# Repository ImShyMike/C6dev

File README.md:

# C6dev

A tiny and low power dev board for the ESP32-C6 with 10 GPIO pins, microSD card slot, 64Mbit (8MB) of Quad SPI Flash, USB C 2.0, a step-down converter for efficiency, 2.4 GHz ceramic chip antenna and very cool silkscreen. All pins are labeled with their number, actual GPIO and even other functions.

---

I've been wanting to make a devboard for a while now so i decided to make one with a RISC-V, low power MCU while breaking out a bunch of useful stuff while still keeping an acceptable amount of GPIO.

It was quite a lot harder than I expected with all the datasheet searching and looking up everything to make sure it works but atleast the routing was quite fun.

---

| PCB front | PCB back |
|:---------:|:--------:|
|  |  |

---

## PCB

---

## BOM

| Item | Quantity | Price (USD) |
|:----:|:--------:|:-----------:|
| PCB  |       1  |         $77 |

---

## 3D Model

[STL (renders on GitHub)](PCB/devboard/devboard.stl)

[STEP](PCB/devboard/devboard.stl)

[WRL (best)](PCB/devboard/devboard.wrl)

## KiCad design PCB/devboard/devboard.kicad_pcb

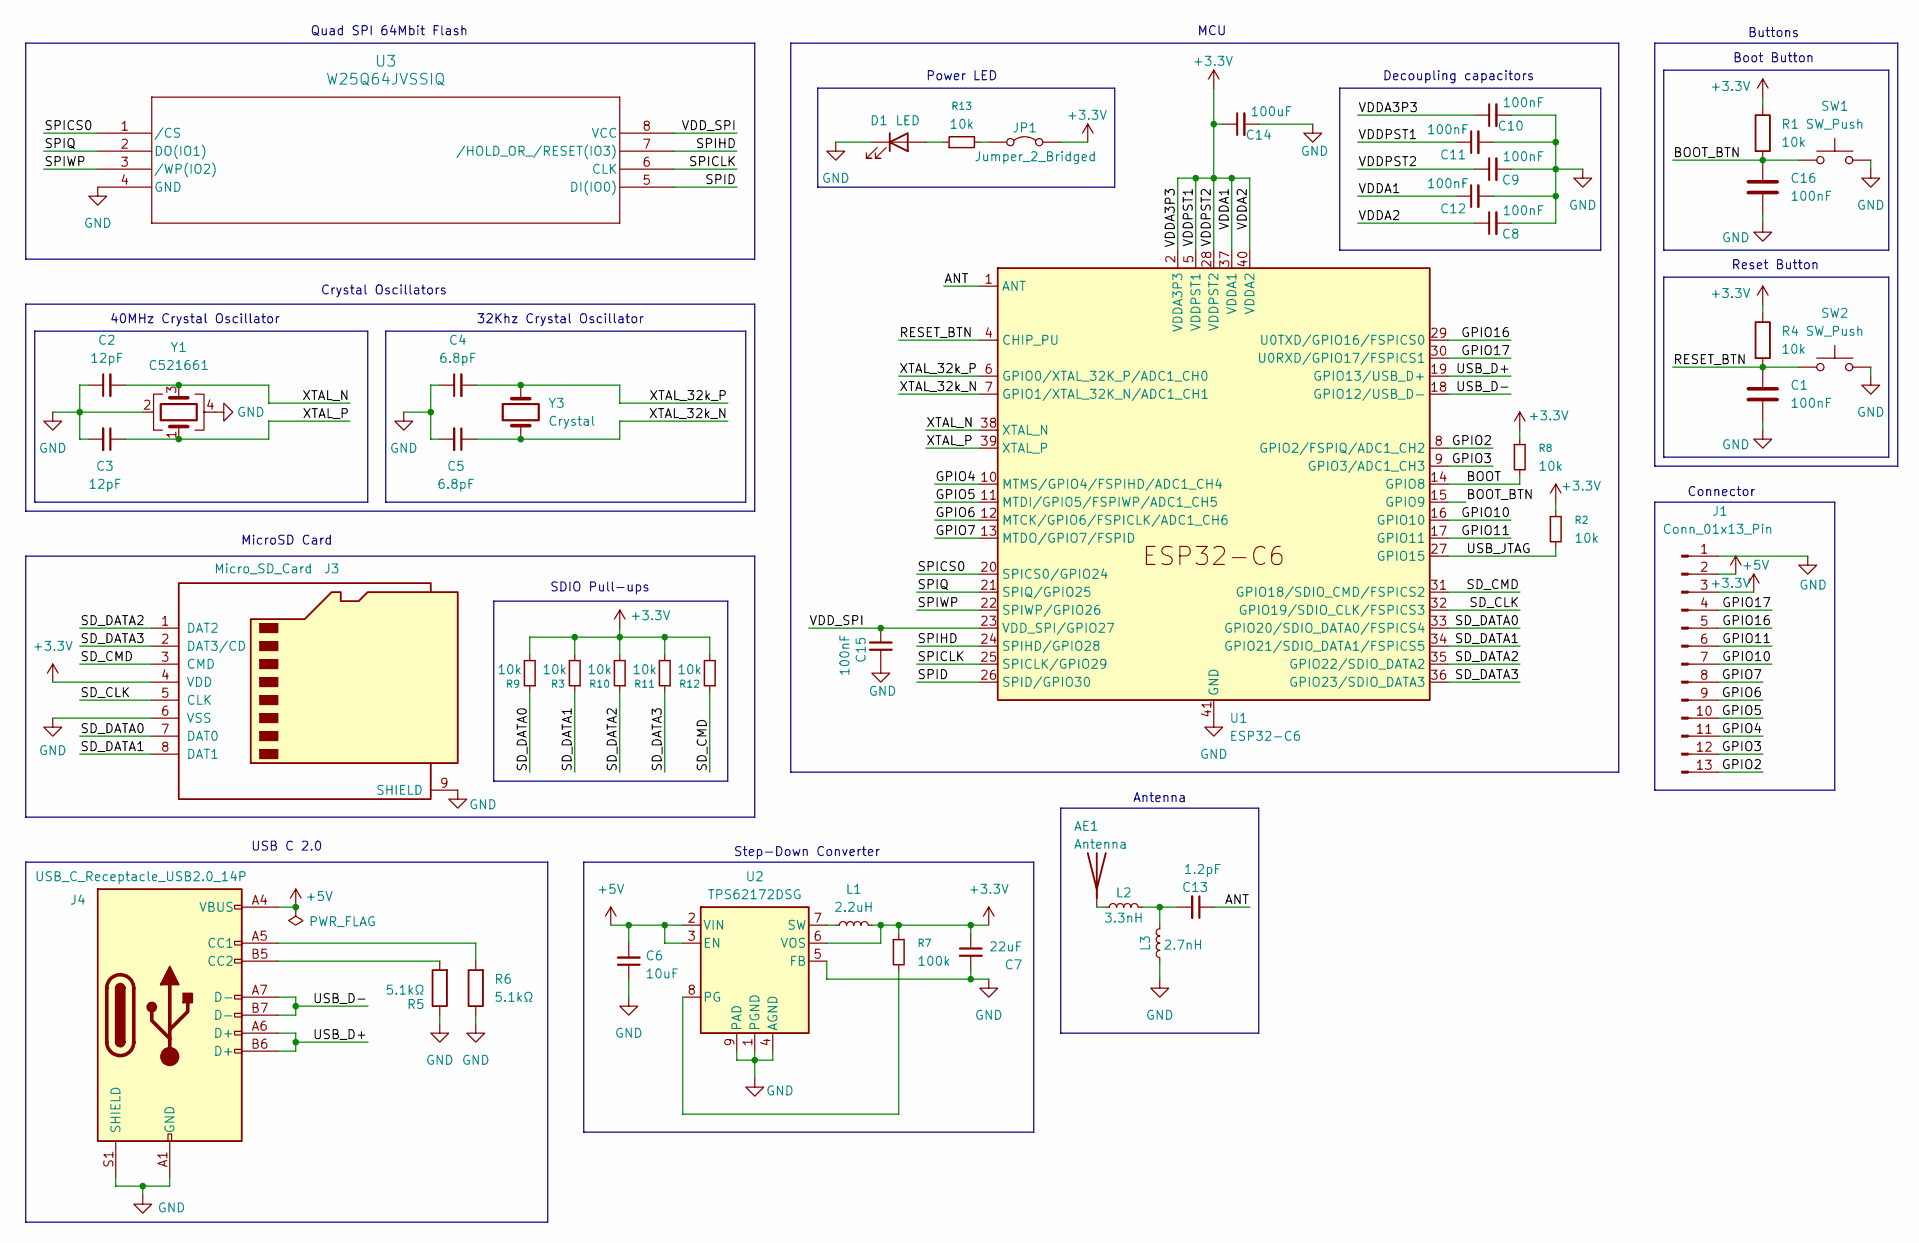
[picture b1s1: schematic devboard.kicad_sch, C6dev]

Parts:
AE1: Antenna; Johanson_2450AT18x100_2400-2500Mhz
C1, C8, C9, C10, C11, C12, C15, C16: 100nF; C_0402_1005Metric
C2, C3: 12pF; C_0402_1005Metric
C4, C5: 6.8pF; C_0402_1005Metric
C6: 10uF; C_0805_2012Metric
C7: 22uF; C_1206_3216Metric
C13: 1.2pF; C_0402_1005Metric
C14: 100uF; CP_EIA-3216-18_Kemet-A
D1: LED; LED_0805_2012Metric
J1: Conn_01x13_Pin; PinHeader_1x13_P2.54mm_Vertical
J3: Micro_SD_Card; microSD_HC_Wuerth_693072010801
J4: USB_C_Receptacle_USB2.0_14P; USB_C_Receptacle_HRO_TYPE-C-31-M-12
JP1: Jumper_2_Bridged; SolderJumper-2_P1.3mm_Open_RoundedPad1.0x1.5mm
L1: 2.2uH; L_0603_1608Metric
L2: 3.3nH; L_0402_1005Metric
L3: 2.7nH; L_0402_1005Metric
R1, R2, R3, R4, R8, R9, R10, R11, R12, R13: 10k; R_0402_1005Metric
R5, R6: 5.1kΩ; R_0402_1005Metric
R7: 100k; R_0402_1005Metric
SW1, SW2: SW_Push; SW_SPST_PTS647_Sx38
U1: ESP32-C6; QFN-40-1EP_5x5mm_P0.4mm_EP3.6x3.6mm
U2: TPS62172DSG; WSON-8-1EP_2x2mm_P0.5mm_EP0.9x1.6mm_ThermalVias
U3: W25Q64JVSSIQ; SOIC-8_5P28X5P28_WIN
Y1: C521661; Crystal_SMD_3225-4Pin_3.2x2.5mm
Y3: Crystal; Crystal_SMD_2012-2Pin_2.0x1.2mm

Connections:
+3.3V: C7.1, C8.1, C9.1, C10.1, C11.1, C12.1, C14.1, J1.3, J3.4 (VDD), JP1.2 (B), L1.2, R1.1, R2.1, R3.2, R4.1, R7.1, R8.1, R9.2, R10.2, R11.2, R12.2, U1.2 (VDDA3P3), U1.3 (VDDA3P3), U1.5 (VDDPST1), U1.28 (VDDPST2), U1.37 (VDDA1), U1.40 (VDDA2), U2.6 (VOS)
+5V: C6.2, J1.2, J4.A4 (VBUS), J4.A9 (VBUS), J4.B4 (VBUS), J4.B9 (VBUS), U2.2 (VIN), U2.3 (EN)
/ANT: C13.1, U1.1 (ANT)
/BOOT: R8.2, U1.14 (GPIO8)
/BOOT_BTN: C16.1, R1.2, SW1.1, U1.15 (GPIO9)
/GPIO2: J1.13, U1.8 (GPIO2/FSPIQ/ADC1_CH2)
/GPIO3: J1.12, U1.9 (GPIO3/ADC1_CH3)
/GPIO4: J1.11, U1.10 (MTMS/GPIO4/FSPIHD/ADC1_CH4)
/GPIO5: J1.10, U1.11 (MTDI/GPIO5/FSPIWP/ADC1_CH5)
/GPIO6: J1.9, U1.12 (MTCK/GPIO6/FSPICLK/ADC1_CH6)
/GPIO7: J1.8, U1.13 (MTDO/GPIO7/FSPID)
/GPIO10: J1.7, U1.16 (GPIO10)
/GPIO11: J1.6, U1.17 (GPIO11)
/GPIO16: J1.5, U1.29 (U0TXD/GPIO16/FSPICS0)
/GPIO17: J1.4, U1.30 (U0RXD/GPIO17/FSPICS1)
/RESET_BTN: C1.1, R4.2, SW2.1, U1.4 (CHIP_PU)
/SD_CLK: J3.5 (CLK), U1.32 (GPIO19/SDIO_CLK/FSPICS3)
/SD_CMD: J3.3 (CMD), R12.1, U1.31 (GPIO18/SDIO_CMD/FSPICS2)
/SD_DATA0: J3.7 (DAT0), R9.1, U1.33 (GPIO20/SDIO_DATA0/FSPICS4)
/SD_DATA1: J3.8 (DAT1), R3.1, U1.34 (GPIO21/SDIO_DATA1/FSPICS5)
/SD_DATA2: J3.1 (DAT2), R10.1, U1.35 (GPIO22/SDIO_DATA2)
/SD_DATA3: J3.2 (DAT3/CD), R11.1, U1.36 (GPIO23/SDIO_DATA3)
/SPICLK: U1.25 (SPICLK/GPIO29), U3.6 (CLK)
/SPICS0: U1.20 (SPICS0/GPIO24), U3.1 (/CS)
/SPID: U1.26 (SPID/GPIO30), U3.5 (DI(IO0))
/SPIHD: U1.24 (SPIHD/GPIO28), U3.7 (/HOLD_OR_/RESET(IO3))
/SPIQ: U1.21 (SPIQ/GPIO25), U3.2 (DO(IO1))
/SPIWP: U1.22 (SPIWP/GPIO26), U3.3 (/WP(IO2))
/USB_D+: J4.A6 (D+), J4.B6 (D+), U1.19 (GPIO13/USB_D+)
/USB_D-: J4.A7 (D-), J4.B7 (D-), U1.18 (GPIO12/USB_D-)
/USB_JTAG: R2.2, U1.27 (GPIO15)
/VDD_SPI: C15.1, U1.23 (VDD_SPI/GPIO27), U3.8 (VCC)
/XTAL_32k_N: C5.1, U1.7 (GPIO1/XTAL_32K_N/ADC1_CH1), Y3.1
/XTAL_32k_P: C4.2, U1.6 (GPIO0/XTAL_32K_P/ADC1_CH0), Y3.2
/XTAL_N: C2.2, U1.38 (XTAL_N), Y1.3
/XTAL_P: C3.1, U1.39 (XTAL_P), Y1.1
GND: C1.2, C2.1, C3.2, C4.1, C5.2, C6.1, C7.2, C8.2, C9.2, C10.2, C11.2, C12.2, C14.2, C15.2, C16.2, D1.1 (K), J1.1, J3.6 (VSS), J3.9 (SHIELD), J4.A1 (GND), J4.A12 (GND), J4.B1 (GND), J4.B12 (GND), J4.S1 (SHIELD), L3.1, R5.1, R6.1, SW1.2, SW2.2, U1.41 (GND), U2.1 (PGND), U2.4 (AGND), U2.5 (FB), U2.9 (PAD), U3.4 (GND), Y1.2, Y1.4
unnamed: AE1.1 (A), L2.1
unnamed: C13.2, L2.2, L3.2
unnamed: D1.2 (A), R13.1
unnamed: J4.A5 (CC1), R6.2
unnamed: J4.B5 (CC2), R5.2
unnamed: JP1.1 (A), R13.2
unnamed: R7.2, U2.8 (PG)
unnamed: L1.1, U2.7 (SW)

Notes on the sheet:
40MHz Crystal Oscillator
MCU
Buttons
USB C 2.0
Connector
Power LED
Decoupling capacitors
32Khz Crystal Oscillator
Crystal Oscillators
Boot Button
Step-Down Converter
Reset Button
Antenna
MicroSD Card
SDIO Pull-ups
Quad SPI 64Mbit Flash

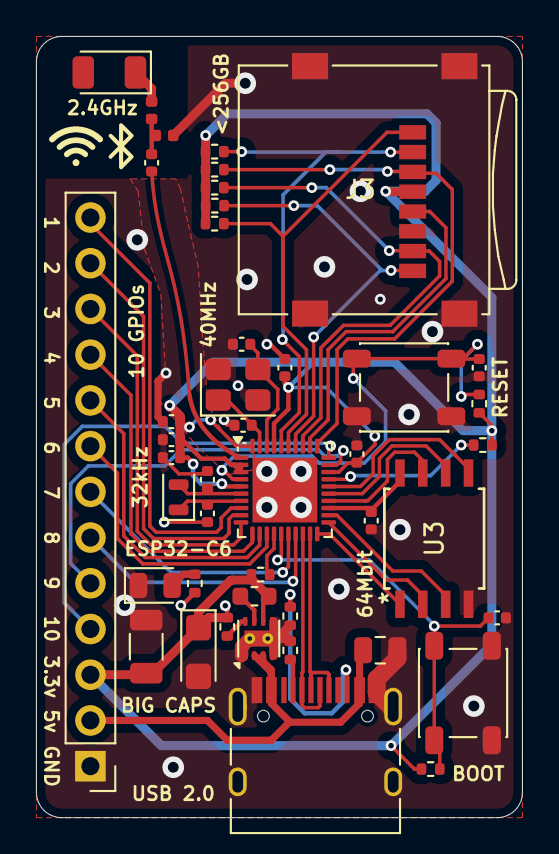
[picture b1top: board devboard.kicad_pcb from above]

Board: 2 copper layers, 27.0 x 43.4 mm, 45 parts (1 on the bottom side), 45 nets.

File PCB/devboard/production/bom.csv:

Designator,Footprint,Quantity,Value,LCSC Part #
AE1,Johanson_2450AT18x100_2400-2500Mhz,1,Antenna,
"C1, C10, C11, C12, C15, C16, C8, C9",0402,8,100nF,
C13,0402,1,1.2pF,
C14,CP_EIA-3216-18_Kemet-A,1,100uF,
"C2, C3",0402,2,12pF,
"C4, C5",0402,2,6.8pF,
C6,0805,1,10uF,
C7,1206,1,22uF,
D1,0805,1,LED,
J1,PinHeader_1x13_P2.54mm_Vertical,1,Conn_01x13_Pin,
J3,microSD_HC_Wuerth_693072010801,1,Micro_SD_Card,
J4,USB_C_Receptacle_HRO_TYPE-C-31-M-12,1,USB_C_Receptacle_USB2.0_14P,
JP1,SolderJumper-2_P1.3mm_Open_RoundedPad1.0x1.5mm,1,Jumper_2_Bridged,
L1,0603,1,2.2uH,
L2,0402,1,3.3nH,
L3,0402,1,2.7nH,
"R1, R10, R11, R12, R13, R2, R3, R4, R8, R9",0402,10,10k,
"R5, R6",0402,2,5.1kΩ,
R7,0402,1,100k,
"SW1, SW2",SW_SPST_PTS647_Sx38,2,SW_Push,
U1,QFN-40-1EP_5x5mm_P0.4mm_EP3.6x3.6mm,1,ESP32-C6,
U2,WSON-8-1EP_2x2mm_P0.5mm_EP0.9x1.6mm_ThermalVias,1,TPS62172DSG,
U3,SOIC-8_5P28X5P28_WIN,1,W25Q64JVSSIQ,
Y1,Crystal_SMD_3225-4Pin_3.2x2.5mm,1,C521661,
Y3,Crystal_SMD_2012-2Pin_2.0x1.2mm,1,Crystal,

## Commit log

2025-07-26 start schematic
2025-07-26 finished schematic
2025-07-27 pcb done :yay:
2025-07-27 move the pcb to the corner
2025-07-27 broken image and formatting
2025-07-27 adjust ant trace
2025-07-27 export pcb
2025-07-27 polishing
2025-07-28 silkscreeeen
2025-07-28 finishing up
2025-07-28 aaaaaaa
2025-07-28 update models
2025-07-28 smaller stl
2025-07-28 add WRL
2025-07-28 fixesss
2025-07-28 aaaaa
